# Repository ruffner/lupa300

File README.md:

# AR/VR FPGA Controller Camera Interface
## Supported Platforms
Work is currently being done to integrate AR functionality into two main platforms. 
### Zynq7000 SoC 
With custom carrier PCB providing 2xHDMI and a LUPA300 CMOS image sensor. 

### Mojo Board v3
With 2 port HDMI shield and Basler USB3 Camera

## Supplementary Tools
The following pieces of software have been written to interface with and control various aspects of the project

- **[Lupa300Viewer/](https://github.com/ruffner/lupa300/tree/master/Lupa300Viewer)** minimal tcp video streaming client software, for live viewing on PC and recording. The Following image shows the streaming setup with an image shown from the LUPA300 sensor before fixed pattern noise (FPN) correction.

These are two example images from the LUPA300 sensor, both before and after FPN correction.

- **[LAUMicroZedBoard/](https://github.com/ruffner/lupa300/tree/master/LAUMicroZedBoard)** headless Qt video server. Retrieves image sensor data from FPGA via [xillybus](http://xillybus.com/). 
- **[tools/Si514_programmer](https://github.com/ruffner/lupa300/tree/master/tools/si514_programmer)** Provides a serial interface for controlling the frequency of an [Si514 programmable oscillator](https://www.silabs.com/documents/public/data-sheets/Si514.pdf) conncted to an Arduino over i2c.
- **[Cusom MojoV3 Firmware](https://github.com/ruffner/mojo-arduino)** adds support for utilization of the 1024 bytes of EEPROM onboard th ATMega32u4 on the [Mojo](https://alchitry.com/products/mojo-v3). 
- -  [Example Python Uploader](https://github.com/ruffner/lupa300/tree/master/tools/mojo_trigger) in a Jupyter notebook, for uploading eeprom values to the Mojo

### Previous Designs
**Before HDMI Integration**

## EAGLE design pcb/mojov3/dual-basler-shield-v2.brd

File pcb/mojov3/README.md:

## Basler Machine Vision Camera Interface Boards

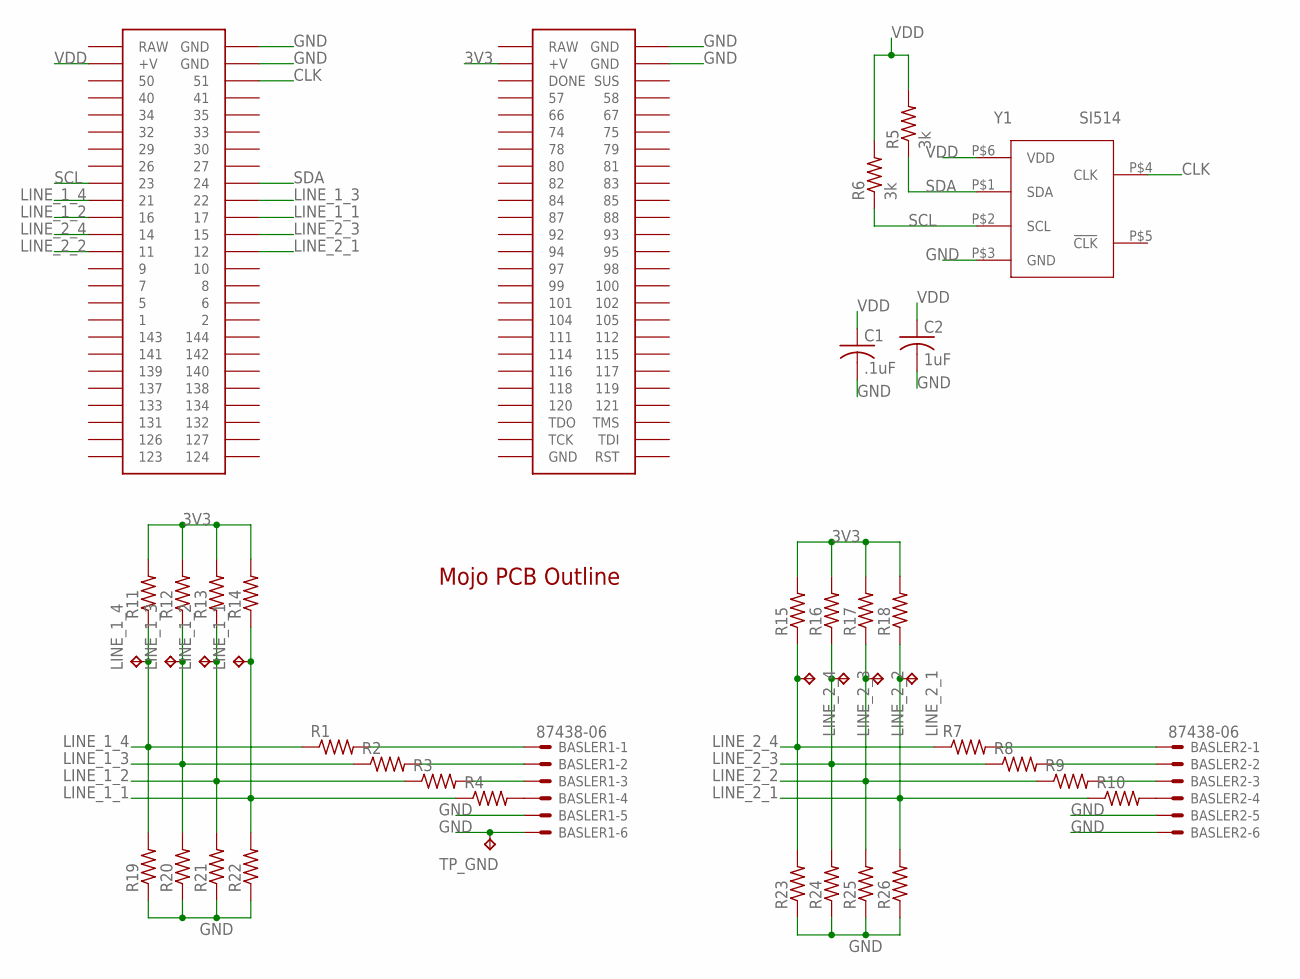
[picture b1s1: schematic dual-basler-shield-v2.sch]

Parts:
BASLER1, BASLER2: 87438-06
C1: .1uF; C0603
C2: 1uF; C0603
LINE_1_1, LINE_1_2, LINE_1_3, LINE_1_4, LINE_2_1, LINE_2_2, LINE_2_3, LINE_2_4: TPTP16R; TP16R
R1, R2, R3, R4, R7, R8, R9, R10, R11, R12, R13, R14, R15, R16, R17, R18, R19, R20, R21, R22, R23, R24, R25, R26: R-US_R0603; R0603
R5, R6: 3k; R0603
TP_GND: TPTP16R; TP16R
U$3: MOJO_OUTLINE
U$4: MOJOV3; MOJO_V3
Y1: SI514; XTAL-6PIN

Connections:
3V3: R11.2, R12.2, R13.2, R14.2, R15.2, R16.2, R17.2, R18.2, U$4.V@2 (+V)
CLK: U$4.51, Y1.P$4 (CLK)
GND: BASLER1.5, BASLER1.6, BASLER2.5, BASLER2.6, C1.2, C2.2, R19.1, R20.1, R21.1, R22.1, R23.1, R24.1, R25.1, R26.1, TP_GND.TP, U$4.GND@1 (GND), U$4.GND@2 (GND), U$4.GND@3 (GND), U$4.GND@4 (GND), Y1.P$3 (GND)
LINE_1_1: LINE_1_1.TP, R4.1, R14.1, R22.2, U$4.17
LINE_1_2: LINE_1_2.TP, R3.1, R13.1, R21.2, U$4.16
LINE_1_3: LINE_1_3.TP, R2.1, R12.1, R20.2, U$4.22
LINE_1_4: LINE_1_4.TP, R1.1, R11.1, R19.2, U$4.21
LINE_2_1: LINE_2_1.TP, R10.1, R18.1, R26.2, U$4.12
LINE_2_2: LINE_2_2.TP, R9.1, R17.1, R25.2, U$4.11
LINE_2_3: LINE_2_3.TP, R8.1, R16.1, R24.2, U$4.15
LINE_2_4: LINE_2_4.TP, R7.1, R15.1, R23.2, U$4.14
unnamed: BASLER1.1, R1.2
unnamed: BASLER1.2, R2.2
unnamed: BASLER1.3, R3.2
unnamed: BASLER1.4, R4.2
unnamed: BASLER2.1, R7.2
unnamed: BASLER2.2, R8.2
unnamed: BASLER2.3, R9.2
unnamed: BASLER2.4, R10.2
SCL: R6.1, U$4.23, Y1.P$2 (SCL)
SDA: R5.1, U$4.24, Y1.P$1 (SDA)
VDD: C1.1, C2.1, R5.2, R6.2, U$4.V@1 (+V), Y1.P$6 (VDD)

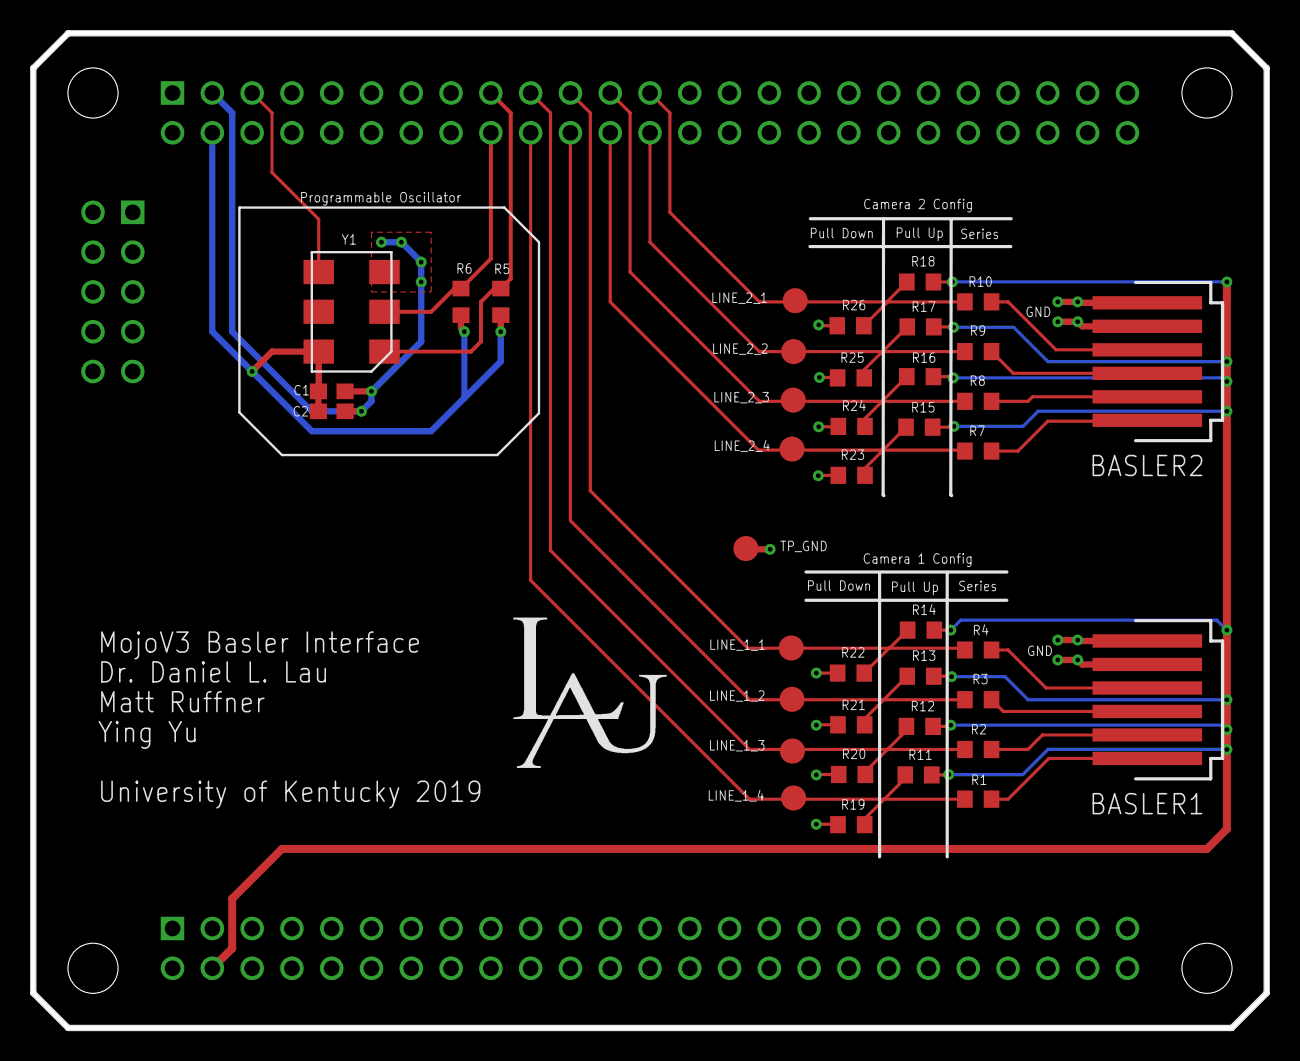
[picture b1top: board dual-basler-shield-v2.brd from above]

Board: 2 copper layers, 78.7 x 63.5 mm, 42 parts (0 on the bottom side), 22 nets.

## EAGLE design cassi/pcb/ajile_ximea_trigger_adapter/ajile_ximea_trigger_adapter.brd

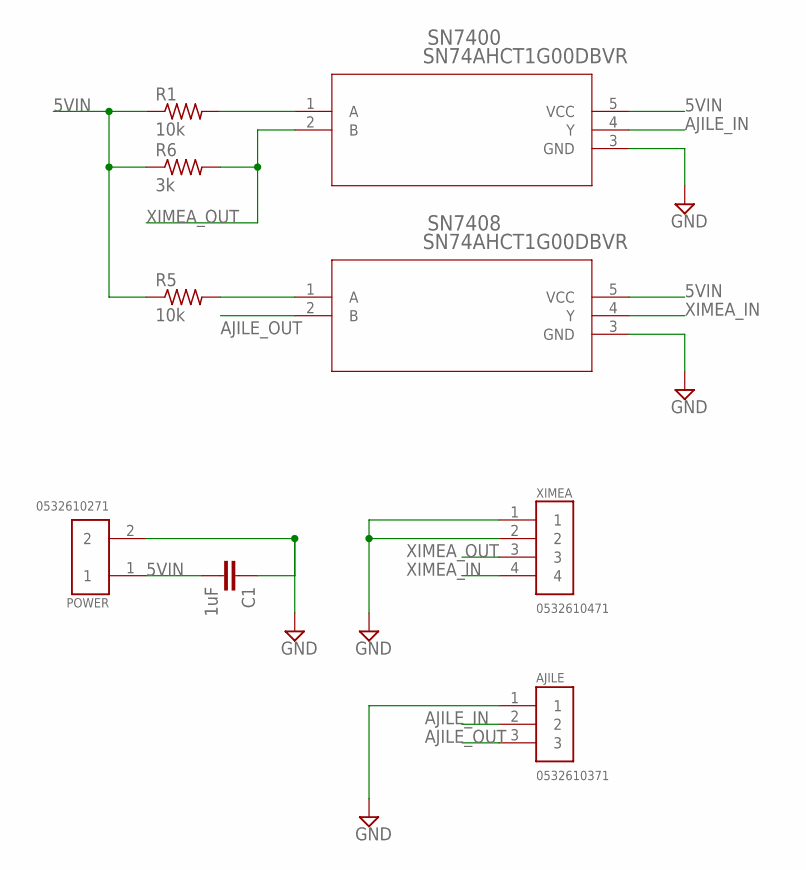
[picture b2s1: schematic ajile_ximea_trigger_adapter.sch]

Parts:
AJILE: 0532610371; MOLEX_0532610371
C1: 1uF; C0603
POWER: 0532610271; MOLEX_0532610271
R1, R5: 10k; R0603
R6: 3k; R0603
SN7400, SN7408: SN74AHCT1G00DBVR; DBV5
XIMEA: 0532610471; MOLEX_0532610471

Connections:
5VIN: C1.2, POWER.1, R1.1, R5.1, R6.1, SN7400.5 (VCC), SN7408.5 (VCC)
AJILE_IN: AJILE.2, SN7400.4 (Y)
AJILE_OUT: AJILE.3, SN7408.2 (B)
GND: AJILE.1, C1.1, POWER.2, SN7400.3 (GND), SN7408.3 (GND), XIMEA.1, XIMEA.2
unnamed: R5.2, SN7408.1 (A)
unnamed: R1.2, SN7400.1 (A)
XIMEA_IN: SN7408.4 (Y), XIMEA.4
XIMEA_OUT: R6.2, SN7400.2 (B), XIMEA.3

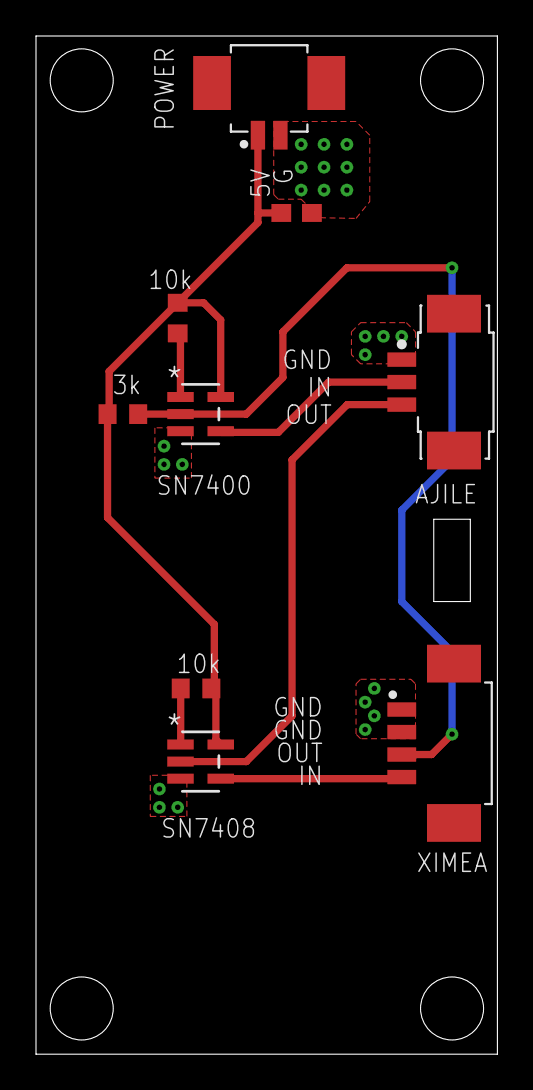
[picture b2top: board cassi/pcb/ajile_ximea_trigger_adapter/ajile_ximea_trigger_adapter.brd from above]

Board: 2 copper layers, 25.6 x 56.6 mm, 9 parts (0 on the bottom side), 8 nets.

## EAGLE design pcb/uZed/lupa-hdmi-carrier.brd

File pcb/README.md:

## AR/VR Machine Vision Camera Interfaces

### Basler Pylon

### XIMEA USB3

### LUPA 300

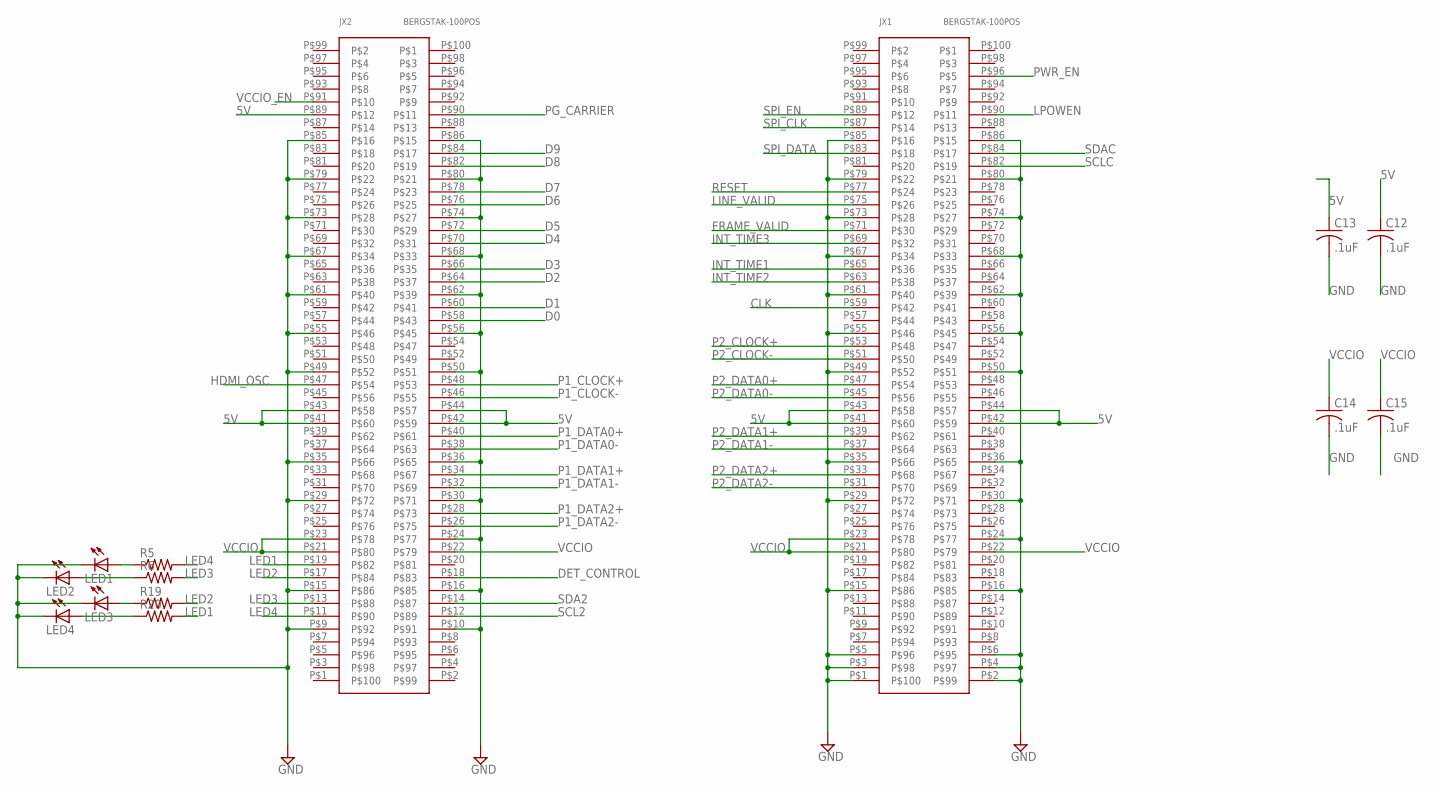
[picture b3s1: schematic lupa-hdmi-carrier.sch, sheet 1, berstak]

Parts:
C12, C13, C14, C15: .1uF; C0603
JX1, JX2: BERGSTAK-100POS; BERG100POS
LED1, LED2, LED3, LED4: LEDCHIPLED_0805; CHIPLED_0805
R5, R6, R19, R20: R-US_R0603; R0603

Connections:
5V: C12.1, C13.1, JX1.P$41, JX1.P$42, JX1.P$43, JX1.P$44, JX2.P$41, JX2.P$42, JX2.P$43, JX2.P$44, JX2.P$89; also elsewhere on the board
CLK: JX1.P$59; also elsewhere on the board
D0: JX2.P$58; also elsewhere on the board
D1: JX2.P$60; also elsewhere on the board
D2: JX2.P$64; also elsewhere on the board
D3: JX2.P$66; also elsewhere on the board
D4: JX2.P$70; also elsewhere on the board
D5: JX2.P$72; also elsewhere on the board
D6: JX2.P$76; also elsewhere on the board
D7: JX2.P$78; also elsewhere on the board
D8: JX2.P$82; also elsewhere on the board
D9: JX2.P$84; also elsewhere on the board
DET_CONTROL: JX2.P$18; also elsewhere on the board
FRAME_VALID: JX1.P$71; also elsewhere on the board
GND: C12.2, C13.2, C14.2, C15.2, JX1.P$1, JX1.P$2, JX1.P$3, JX1.P$4, JX1.P$5, JX1.P$6, JX1.P$15, JX1.P$16, JX1.P$24, JX1.P$29, JX1.P$30, JX1.P$35, JX1.P$36, JX1.P$49, JX1.P$50, JX1.P$55, JX1.P$56, JX1.P$61, JX1.P$62, JX1.P$67, JX1.P$68, JX1.P$73, JX1.P$74, JX1.P$79, JX1.P$80, JX1.P$85, JX1.P$86, JX2.P$9, JX2.P$10, JX2.P$15, JX2.P$16, JX2.P$24, JX2.P$29, JX2.P$30, JX2.P$35, JX2.P$36, JX2.P$49, JX2.P$50, JX2.P$55, JX2.P$56, JX2.P$61, JX2.P$62, JX2.P$67, JX2.P$68, JX2.P$73, JX2.P$74, JX2.P$79, JX2.P$80, JX2.P$85, JX2.P$86, LED1.C, LED2.C, LED3.C, LED4.C; also elsewhere on the board
HDMI_OSC: JX2.P$47; also elsewhere on the board
INT_TIME1: JX1.P$65; also elsewhere on the board
INT_TIME2: JX1.P$63; also elsewhere on the board
INT_TIME3: JX1.P$69; also elsewhere on the board
LED1: JX2.P$19, R20.2
LED2: JX2.P$17, R19.2
LED3: JX2.P$13, R6.2
LED4: JX2.P$11, R5.2
LINE_VALID: JX1.P$75; also elsewhere on the board
LPOWEN: JX1.P$90; also elsewhere on the board
unnamed: LED1.A, R5.1
unnamed: LED2.A, R6.1
unnamed: LED3.A, R19.1
unnamed: LED4.A, R20.1
P1_CLOCK+: JX2.P$48; also elsewhere on the board
P1_CLOCK-: JX2.P$46; also elsewhere on the board
P1_DATA0+: JX2.P$40; also elsewhere on the board
P1_DATA0-: JX2.P$38; also elsewhere on the board
P1_DATA1+: JX2.P$34; also elsewhere on the board
P1_DATA1-: JX2.P$32; also elsewhere on the board
P1_DATA2+: JX2.P$28; also elsewhere on the board
P1_DATA2-: JX2.P$26; also elsewhere on the board
P2_CLOCK+: JX1.P$53; also elsewhere on the board
P2_CLOCK-: JX1.P$51; also elsewhere on the board
P2_DATA0+: JX1.P$47; also elsewhere on the board
P2_DATA0-: JX1.P$45; also elsewhere on the board
P2_DATA1+: JX1.P$39; also elsewhere on the board
P2_DATA1-: JX1.P$37; also elsewhere on the board
P2_DATA2+: JX1.P$33; also elsewhere on the board
P2_DATA2-: JX1.P$31; also elsewhere on the board
PG_CARRIER: JX2.P$90
PWR_EN: JX1.P$96; also elsewhere on the board
RESET: JX1.P$77; also elsewhere on the board
SCL2: JX2.P$12; also elsewhere on the board
SCLC: JX1.P$82; also elsewhere on the board
SDA2: JX2.P$14; also elsewhere on the board
SDAC: JX1.P$84; also elsewhere on the board
SPI_CLK: JX1.P$87; also elsewhere on the board
SPI_DATA: JX1.P$83; also elsewhere on the board
SPI_EN: JX1.P$89; also elsewhere on the board
VCCIO: C14.1, C15.1, JX1.P$21, JX1.P$22, JX1.P$23, JX2.P$21, JX2.P$22, JX2.P$23; also elsewhere on the board
VCCIO_EN: JX2.P$91; also elsewhere on the board

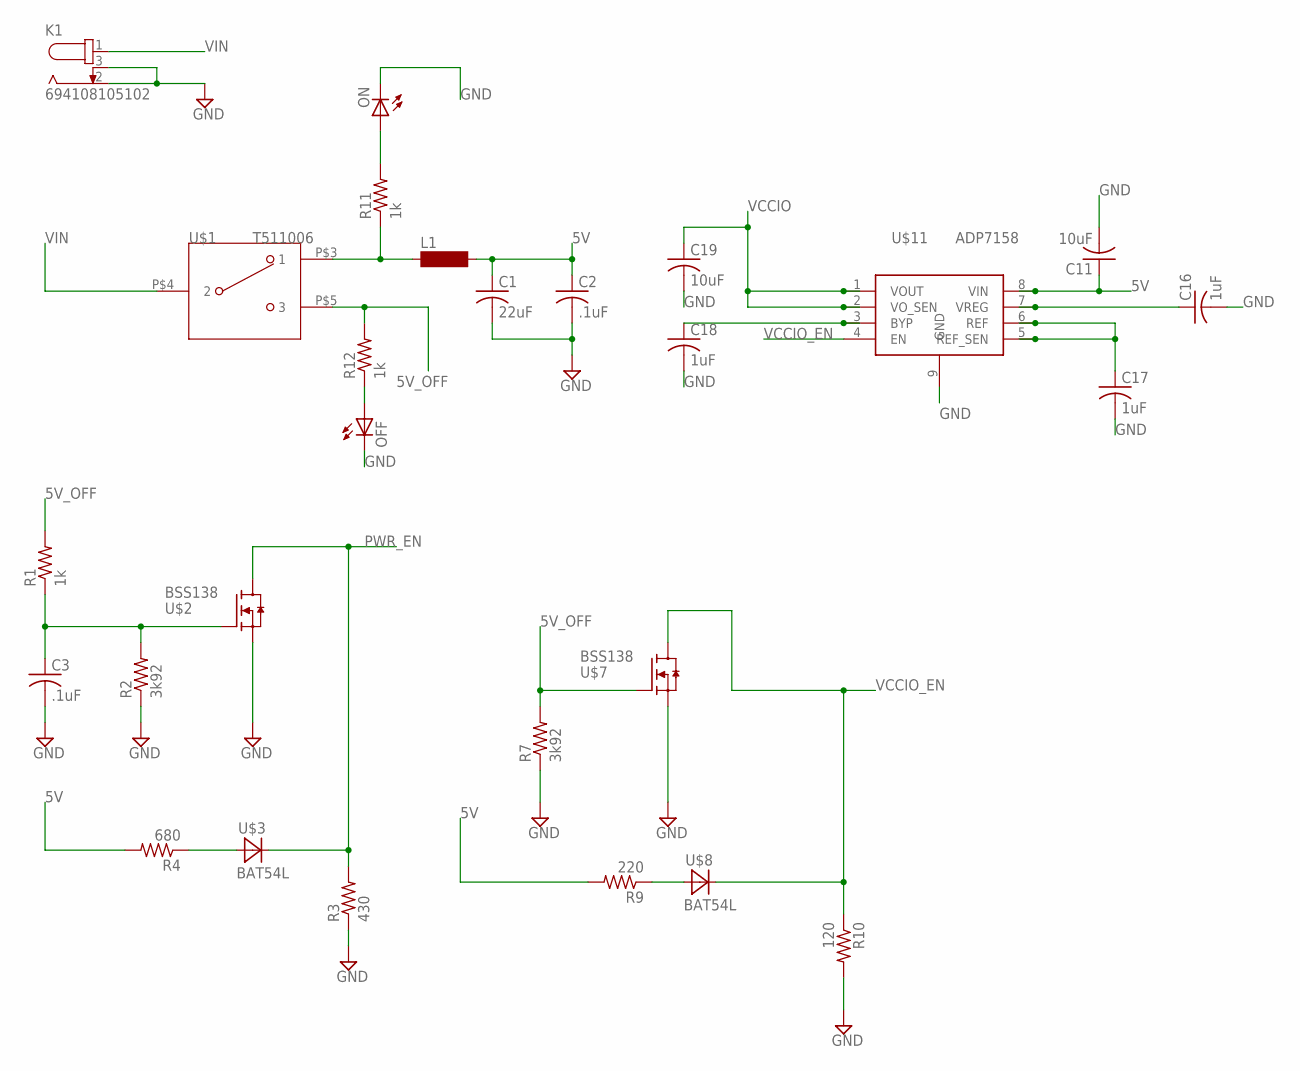
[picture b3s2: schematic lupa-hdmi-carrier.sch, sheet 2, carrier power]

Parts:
C1: 22uF; C1206
C2, C3: .1uF; C0603
C11, C19: 10uF; C0603
C16, C17, C18: 1uF; C0603
K1: 694108105102
L1: MS85
OFF: LEDCHIPLED_0805; CHIPLED_0805
ON: LEDCHIPLED_0805; CHIPLED_0805
R1, R11, R12: 1k; R0603
R2, R7: 3k92; R0603
R3: 430; R0603
R4: 680; R0603
R9: 220; R0603
R10: 120; R0603
U$1: T511006; SPDT
U$2, U$7: BSS138; SOT23
U$3, U$8: BAT54L; SOT23
U$11: ADP7158; SO08

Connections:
5V: C1.1, C2.1, C11.1, L1.2, R4.2, R9.2, U$11.8 (VIN); also elsewhere on the board
5V_OFF: R1.2, R7.2, R12.2, U$1.P$5 (3), U$7.1 (G)
GND: C1.2, C2.2, C3.2, C11.2, C16.2, C17.2, C18.2, C19.2, K1.2, K1.3, OFF.C, ON.C, R2.1, R3.1, R7.1, R10.2, U$2.2 (S), U$7.2 (S), U$11.9 (GND); also elsewhere on the board
unnamed: C3.1, R1.1, R2.2, U$2.1 (G)
unnamed: R4.1, U$3.1 (A)
unnamed: ON.A, R11.2
unnamed: L1.1, R11.1, U$1.P$3 (1)
unnamed: R9.1, U$8.1 (A)
unnamed: C16.1, U$11.7 (VREG)
unnamed: C17.1, U$11.5 (REF_SEN), U$11.6 (REF)
unnamed: C18.1, U$11.3 (BYP)
unnamed: OFF.A, R12.1
PWR_EN: R3.2, U$2.3 (D), U$3.3 (C); also elsewhere on the board
VCCIO: C19.1, U$11.1 (VOUT), U$11.2 (VO_SEN); also elsewhere on the board
VCCIO_EN: R10.1, U$7.3 (D), U$8.3 (C), U$11.4 (EN); also elsewhere on the board
VIN: K1.1, U$1.P$4 (2)

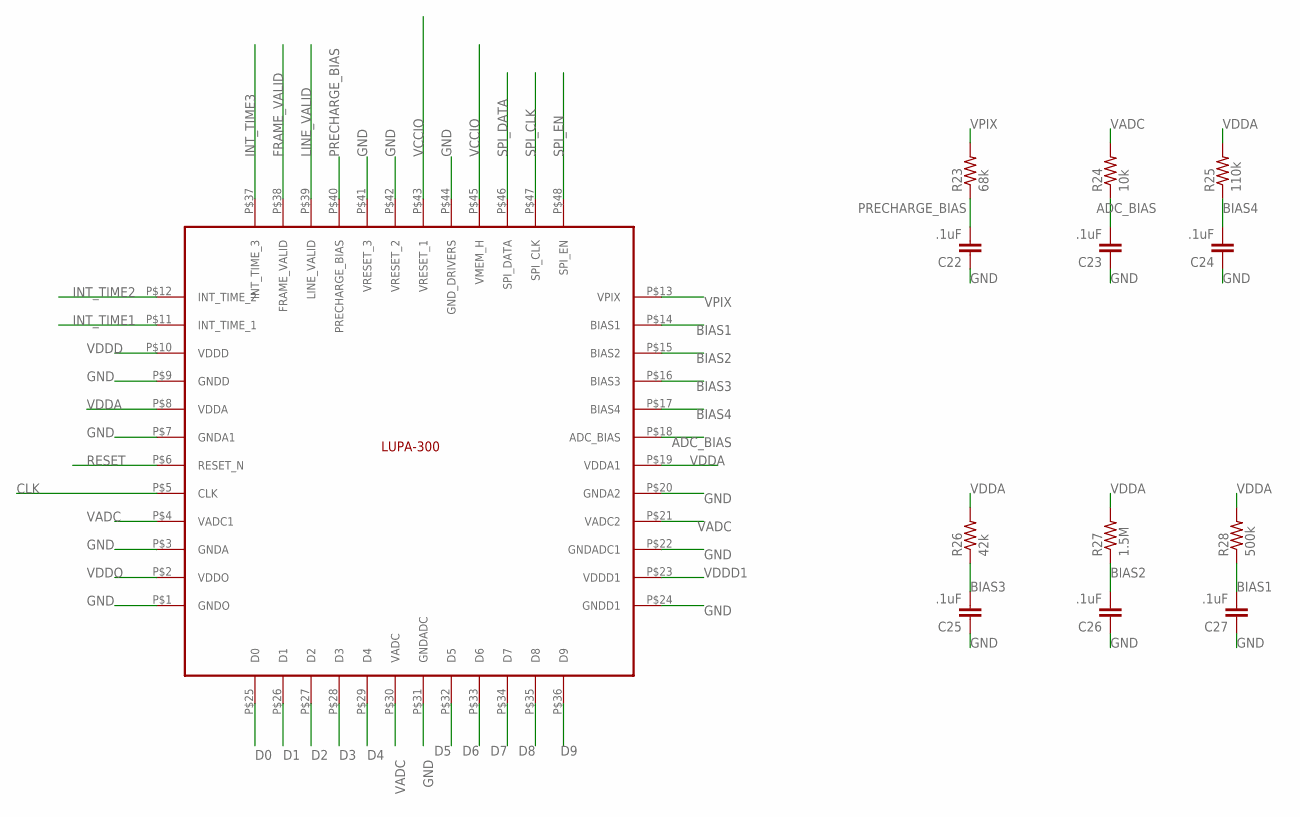
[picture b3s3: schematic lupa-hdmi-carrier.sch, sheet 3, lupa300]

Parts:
C22, C23, C24, C25, C26, C27: .1uF; C0603
R23: 68k; R0603
R24: 10k; R0603
R25: 110k; R0603
R26: 42k; R0603
R27: 1.5M; R0603
R28: 500k; R0603
U$4: LUPA300

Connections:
ADC_BIAS: C23.2, R24.1, U$4.P$18 (ADC_BIAS)
BIAS1: C27.2, R28.1, U$4.P$14 (BIAS1)
BIAS2: C26.2, R27.1, U$4.P$15 (BIAS2)
BIAS3: C25.2, R26.1, U$4.P$16 (BIAS3)
BIAS4: C24.2, R25.1, U$4.P$17 (BIAS4)
CLK: U$4.P$5 (CLK); also elsewhere on the board
D0: U$4.P$25 (D0); also elsewhere on the board
D1: U$4.P$26 (D1); also elsewhere on the board
D2: U$4.P$27 (D2); also elsewhere on the board
D3: U$4.P$28 (D3); also elsewhere on the board
D4: U$4.P$29 (D4); also elsewhere on the board
D5: U$4.P$32 (D5); also elsewhere on the board
D6: U$4.P$33 (D6); also elsewhere on the board
D7: U$4.P$34 (D7); also elsewhere on the board
D8: U$4.P$35 (D8); also elsewhere on the board
D9: U$4.P$36 (D9); also elsewhere on the board
FRAME_VALID: U$4.P$38 (FRAME_VALID); also elsewhere on the board
GND: C22.1, C23.1, C24.1, C25.1, C26.1, C27.1, U$4.P$1 (GNDO), U$4.P$3 (GNDA), U$4.P$7 (GNDA1), U$4.P$9 (GNDD), U$4.P$20 (GNDA2), U$4.P$22 (GNDADC1), U$4.P$24 (GNDD1), U$4.P$31 (GNDADC), U$4.P$41 (VRESET_3), U$4.P$42 (VRESET_2), U$4.P$44 (GND_DRIVERS); also elsewhere on the board
INT_TIME1: U$4.P$11 (INT_TIME_1); also elsewhere on the board
INT_TIME2: U$4.P$12 (INT_TIME_2); also elsewhere on the board
INT_TIME3: U$4.P$37 (INT_TIME_3); also elsewhere on the board
LINE_VALID: U$4.P$39 (LINE_VALID); also elsewhere on the board
PRECHARGE_BIAS: C22.2, R23.1, U$4.P$40 (PRECHARGE_BIAS)
RESET: U$4.P$6 (RESET_N); also elsewhere on the board
SPI_CLK: U$4.P$47 (SPI_CLK); also elsewhere on the board
SPI_DATA: U$4.P$46 (SPI_DATA); also elsewhere on the board
SPI_EN: U$4.P$48 (SPI_EN); also elsewhere on the board
VADC: R24.2, U$4.P$4 (VADC1), U$4.P$21 (VADC2), U$4.P$30 (VADC); also elsewhere on the board
VCCIO: U$4.P$43 (VRESET_1), U$4.P$45 (VMEM_H); also elsewhere on the board
VDDA: R25.2, R26.2, R27.2, R28.2, U$4.P$8 (VDDA), U$4.P$19 (VDDA1); also elsewhere on the board
VDDD: U$4.P$10 (VDDD); also elsewhere on the board
VDDD1: U$4.P$23 (VDDD1); also elsewhere on the board
VDDO: U$4.P$2 (VDDO); also elsewhere on the board
VPIX: R23.2, U$4.P$13 (VPIX); also elsewhere on the board

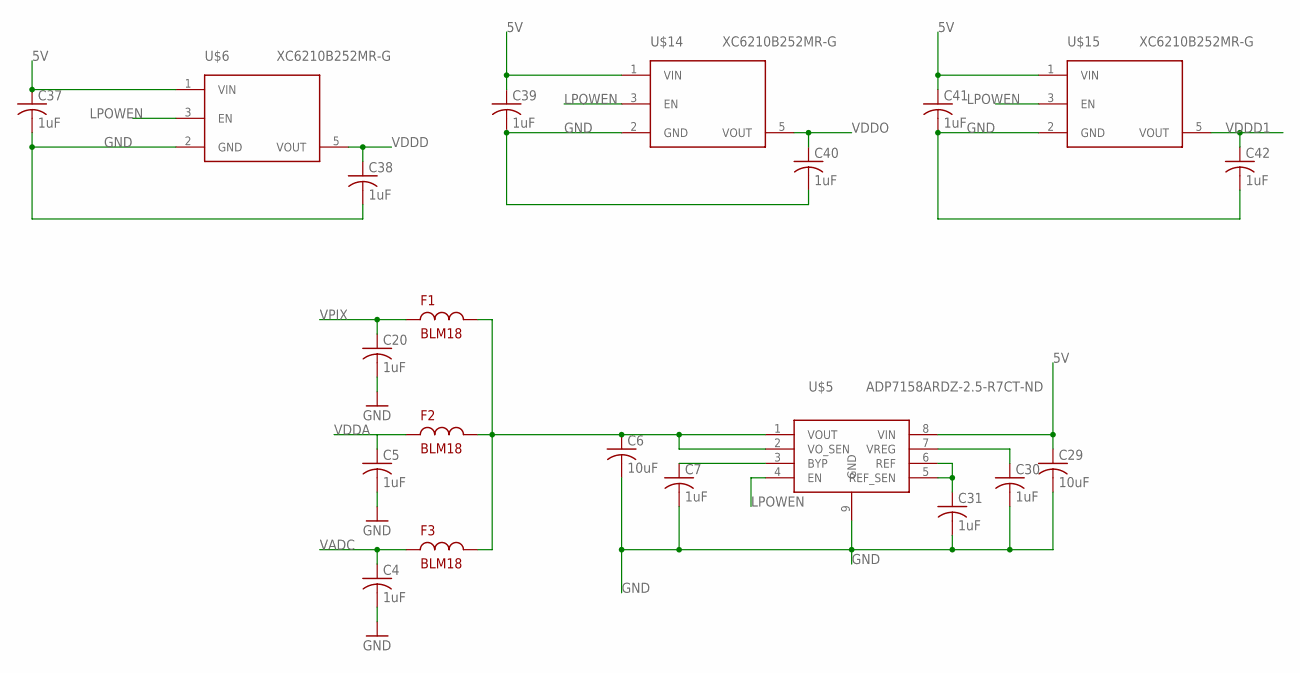
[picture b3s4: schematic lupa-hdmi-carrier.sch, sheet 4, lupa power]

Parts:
C4, C5, C7, C20, C30, C31, C37, C38, C39, C40, C41, C42: 1uF; C0603
C6, C29: 10uF; C0603
F1, F2, F3: BLM18; C0603K
U$5: ADP7158ARDZ-2.5-R7CT-ND; SO08
U$6, U$14, U$15: XC6210B252MR-G; SOT25

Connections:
5V: C29.1, C37.1, C39.1, C41.1, U$5.8 (VIN), U$6.1 (VIN), U$14.1 (VIN), U$15.1 (VIN); also elsewhere on the board
GND: C4.2, C5.2, C6.2, C7.2, C20.2, C29.2, C30.2, C31.2, C37.2, C38.2, C39.2, C40.2, C41.2, C42.2, U$5.9 (GND), U$6.2 (GND), U$14.2 (GND), U$15.2 (GND); also elsewhere on the board
LPOWEN: U$5.4 (EN), U$6.3 (EN), U$14.3 (EN), U$15.3 (EN); also elsewhere on the board
unnamed: C6.1, F1.2, F2.2, F3.2, U$5.1 (VOUT), U$5.2 (VO_SEN)
unnamed: C7.1, U$5.3 (BYP)
unnamed: C30.1, U$5.7 (VREG)
unnamed: C31.1, U$5.5 (REF_SEN), U$5.6 (REF)
VADC: C4.1, F3.1; also elsewhere on the board
VDDA: C5.1, F2.1; also elsewhere on the board
VDDD: C38.1, U$6.5 (VOUT); also elsewhere on the board
VDDD1: C42.1, U$15.5 (VOUT); also elsewhere on the board
VDDO: C40.1, U$14.5 (VOUT); also elsewhere on the board
VPIX: C20.1, F1.1; also elsewhere on the board

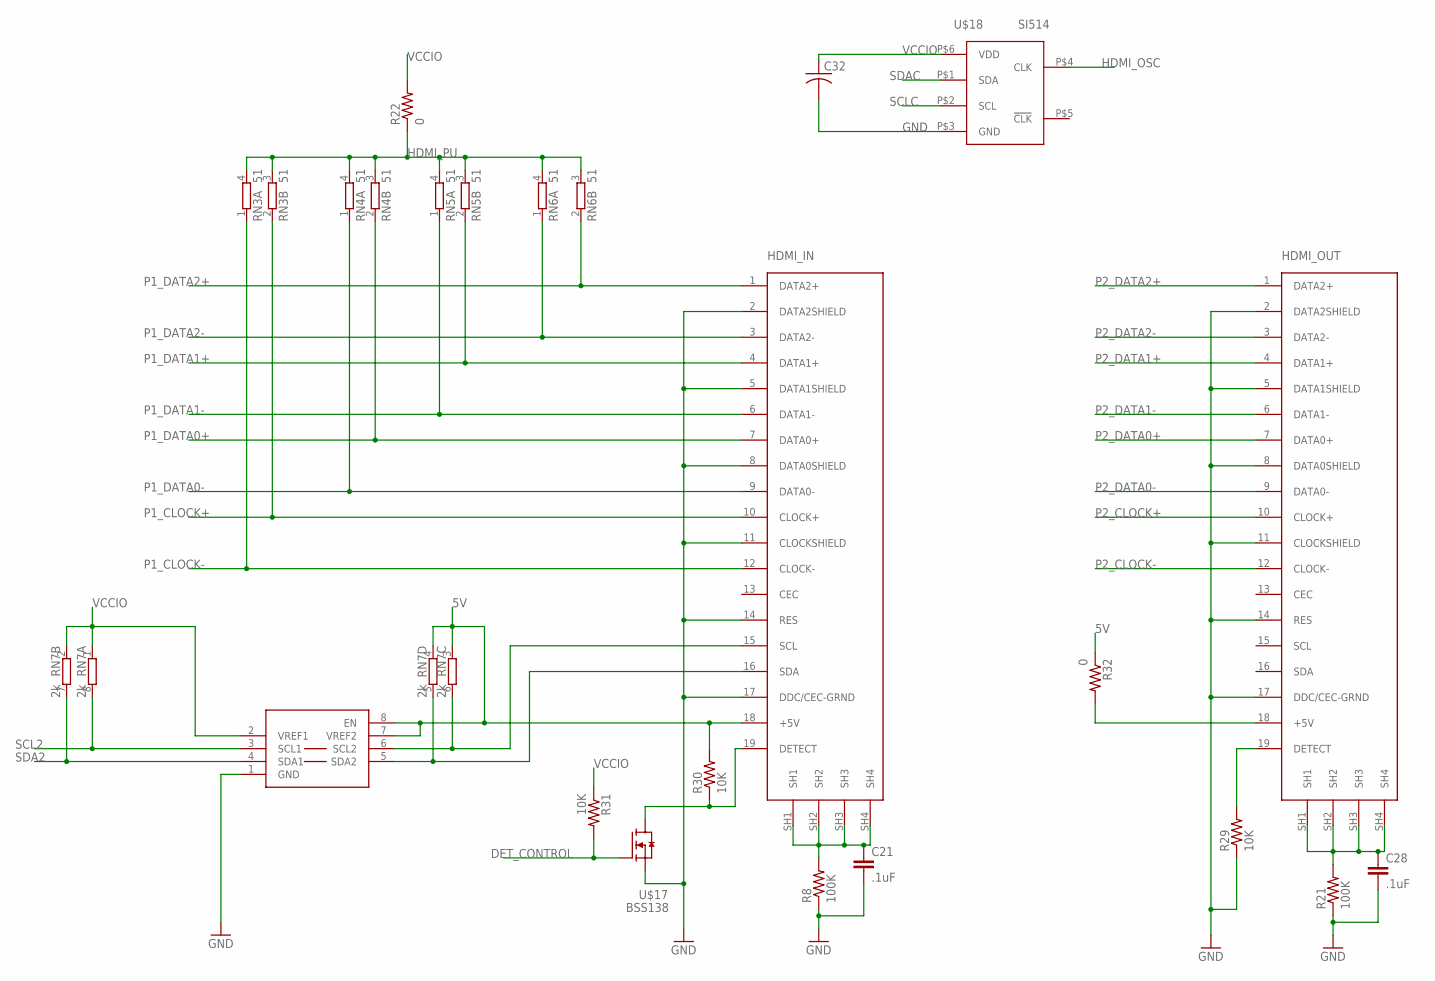
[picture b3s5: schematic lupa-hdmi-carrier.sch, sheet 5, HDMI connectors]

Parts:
C21, C28: .1uF; C0603K
C32: C-USC0603; C0603
HDMI_IN: HDMI-TYPE-A-RECEPTICALFCI10029449; FCI-HDMI-TYPE-A-RECEPT
HDMI_OUT: HDMI-TYPE-A-RECEPTICALFCI10029449; FCI-HDMI-TYPE-A-RECEPT
PCA9306: PCA9306; PSOP-8
R8, R21: 100K; R0603
R22, R32: 0; R0603
R29, R30, R31: 10K; R0603
RN3, RN4, RN5, RN6: 51; EXB34V
RN7: 2k; 0603-ARV
U$17: BSS138; SOT23
U$18: SI514; XTAL-6PIN

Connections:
5V: HDMI_IN.18 (+5V), PCA9306.7 (VREF2), PCA9306.8 (EN), R30.2, R32.1, RN7.3 (1), RN7.4 (1); also elsewhere on the board
DET_CONTROL: R31.2, U$17.1 (G); also elsewhere on the board
GND: C21.2, C28.2, C32.2, HDMI_IN.2 (DATA2SHIELD), HDMI_IN.5 (DATA1SHIELD), HDMI_IN.8 (DATA0SHIELD), HDMI_IN.11 (CLOCKSHIELD), HDMI_IN.14 (RES), HDMI_IN.17 (DDC/CEC-GRND), HDMI_OUT.2 (DATA2SHIELD), HDMI_OUT.5 (DATA1SHIELD), HDMI_OUT.8 (DATA0SHIELD), HDMI_OUT.11 (CLOCKSHIELD), HDMI_OUT.14 (RES), HDMI_OUT.17 (DDC/CEC-GRND), PCA9306.1 (GND), R8.1, R21.1, R29.1, U$17.2 (S), U$18.P$3 (GND); also elsewhere on the board
HDMI_OSC: U$18.P$4 (CLK); also elsewhere on the board
HDMI_PU: R22.1, RN3.3 (2), RN3.4 (2), RN4.3 (2), RN4.4 (2), RN5.3 (2), RN5.4 (2), RN6.3 (2), RN6.4 (2)
unnamed: C28.1, HDMI_OUT.SH1, HDMI_OUT.SH2, HDMI_OUT.SH3, HDMI_OUT.SH4, R21.2
unnamed: HDMI_OUT.19 (DETECT), R29.2
unnamed: HDMI_IN.19 (DETECT), R30.1, U$17.3 (D)
unnamed: HDMI_IN.16 (SDA), PCA9306.5 (SDA2), RN7.5 (2)
unnamed: HDMI_IN.15 (SCL), PCA9306.6 (SCL2), RN7.6 (2)
unnamed: HDMI_OUT.18 (+5V), R32.2
unnamed: C21.1, HDMI_IN.SH1, HDMI_IN.SH2, HDMI_IN.SH3, HDMI_IN.SH4, R8.2
P1_CLOCK+: HDMI_IN.10 (CLOCK+), RN3.2 (1); also elsewhere on the board
P1_CLOCK-: HDMI_IN.12 (CLOCK-), RN3.1; also elsewhere on the board
P1_DATA0+: HDMI_IN.7 (DATA0+), RN4.2 (1); also elsewhere on the board
P1_DATA0-: HDMI_IN.9 (DATA0-), RN4.1; also elsewhere on the board
P1_DATA1+: HDMI_IN.4 (DATA1+), RN5.2 (1); also elsewhere on the board
P1_DATA1-: HDMI_IN.6 (DATA1-), RN5.1; also elsewhere on the board
P1_DATA2+: HDMI_IN.1 (DATA2+), RN6.2 (1); also elsewhere on the board
P1_DATA2-: HDMI_IN.3 (DATA2-), RN6.1; also elsewhere on the board
P2_CLOCK+: HDMI_OUT.10 (CLOCK+); also elsewhere on the board
P2_CLOCK-: HDMI_OUT.12 (CLOCK-); also elsewhere on the board
P2_DATA0+: HDMI_OUT.7 (DATA0+); also elsewhere on the board
P2_DATA0-: HDMI_OUT.9 (DATA0-); also elsewhere on the board
P2_DATA1+: HDMI_OUT.4 (DATA1+); also elsewhere on the board
P2_DATA1-: HDMI_OUT.6 (DATA1-); also elsewhere on the board
P2_DATA2+: HDMI_OUT.1 (DATA2+); also elsewhere on the board
P2_DATA2-: HDMI_OUT.3 (DATA2-); also elsewhere on the board
SCL2: PCA9306.3 (SCL1), RN7.8 (2); also elsewhere on the board
SCLC: U$18.P$2 (SCL); also elsewhere on the board
SDA2: PCA9306.4 (SDA1), RN7.7 (2); also elsewhere on the board
SDAC: U$18.P$1 (SDA); also elsewhere on the board
VCCIO: C32.1, PCA9306.2 (VREF1), R22.2, R31.1, RN7.1, RN7.2 (1), U$18.P$6 (VDD); also elsewhere on the board

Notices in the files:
parts and their libraries:
Wurth_Elektronik_Electromechanic_DC_Powe: Copyright: Würth Elektronik
